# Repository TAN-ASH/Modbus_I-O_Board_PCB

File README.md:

# Modbus_I-O_Board_PCB
Modbus Protocol based Input/output board to control periphery

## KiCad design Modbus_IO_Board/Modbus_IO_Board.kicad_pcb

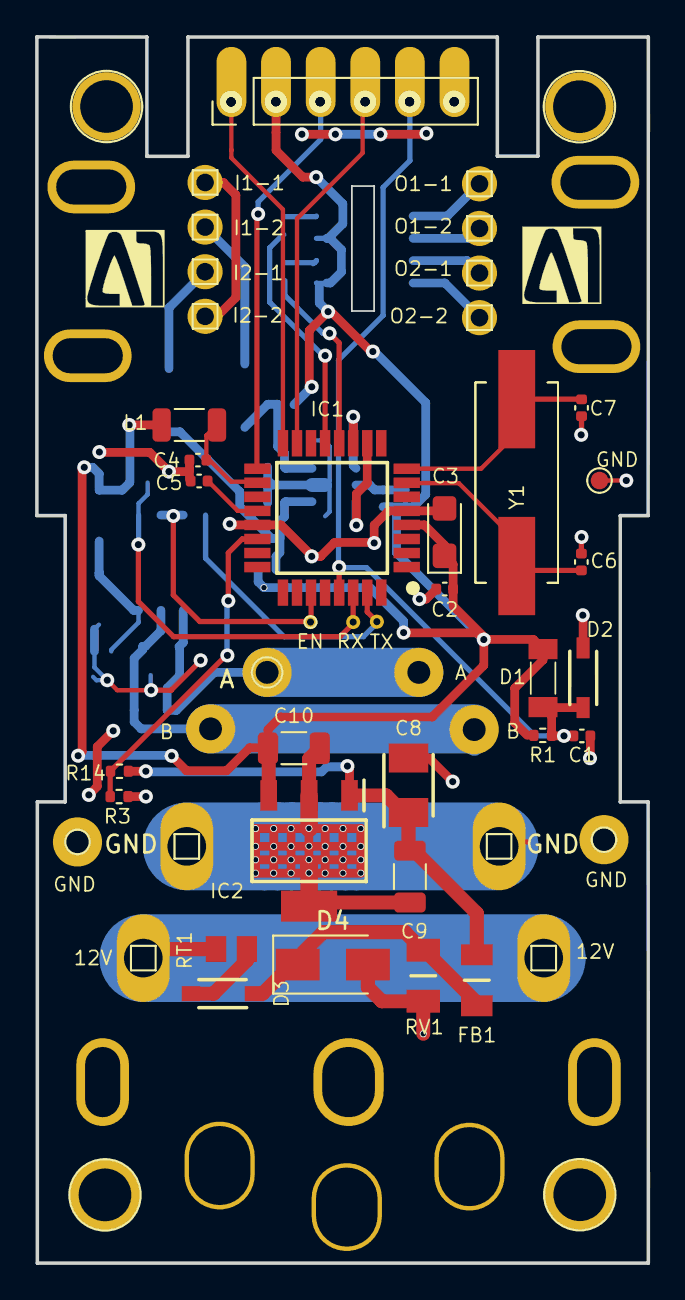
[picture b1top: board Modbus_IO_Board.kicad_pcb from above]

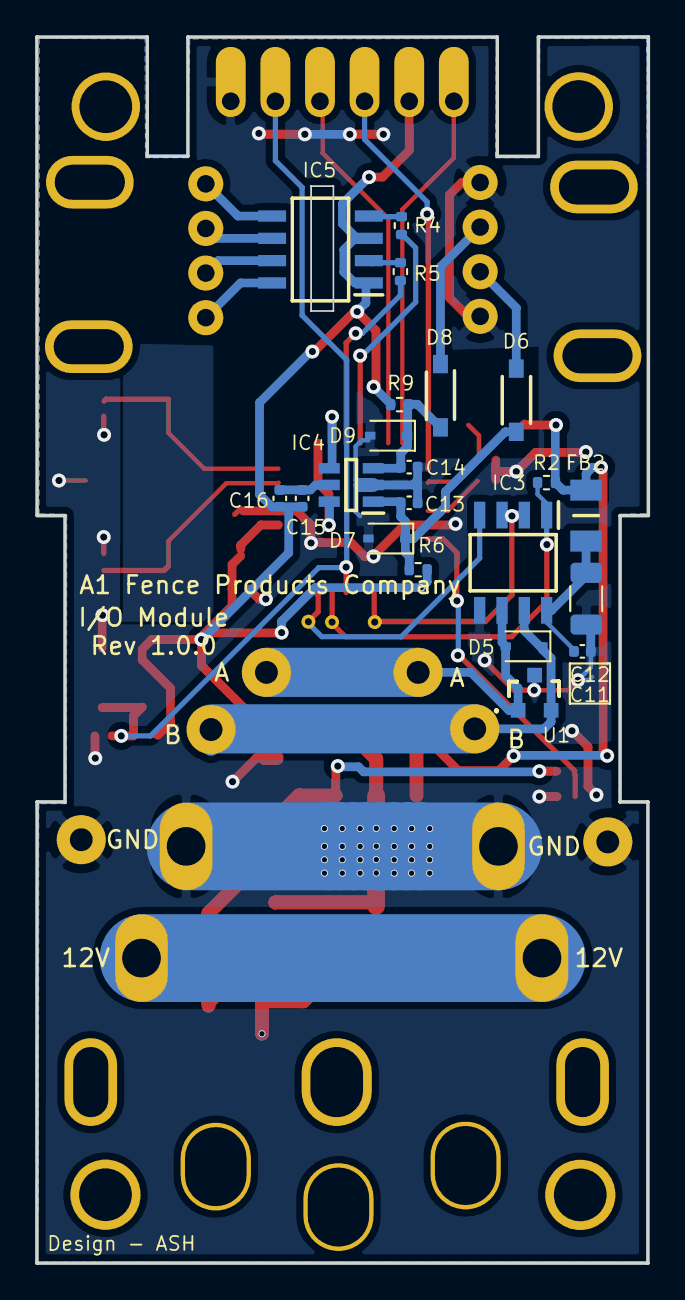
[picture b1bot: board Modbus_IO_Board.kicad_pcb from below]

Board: 2 copper layers, 34.8 x 69.8 mm, 76 parts (21 on the bottom side), 36 nets.

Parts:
12V, 12V#2: TestPoint; TestPoint_THTPad_1.0x1.0mm_Drill0.5mm
A: TestPoint; TestPoint_THTPad_1.0x1.0mm_Drill0.5mm
B: TestPoint; TestPoint_THTPad_1.0x1.0mm_Drill0.5mm
B#2: TestPoint; TestPoint_THTPad_1.0x1.0mm_Drill0.5mm
C1, C16: 1uF; C_0402_1005Metric
C2: 10nF; C_0402_1005Metric
C3: 1uF; CP_EIA-3216-18_Kemet-A
C4, C5, C11, C13, C14: 100nF; C_0402_1005Metric
C6, C7: 22pF; C_0402_1005Metric
C8: 10uF35V; CAPPM3528X210N
C9: 0.1uF35V; C_1206_3216Metric
C10: 4.7uF10V; C_1206_3216Metric
C12: 4.7uF; C_1206_3216Metric
C15: 0.1uF; C_0402_1005Metric
D1: D; FDLL4448
D2: D_Zener; SOD3716X145N
D3, D6, D8: B5819W-TP; SOD3716X135N
D4: D_TVS; D_SMA
D5, D7, D9: D_TVS; D_SOD-323
EN: TestPoint; TestPoint_Pad_D1.0mm
FB1, FB2: 74279218; BEADC3216X130N
GND: TestPoint; TestPoint_Pad_D1.0mm
GND#2, GND#3: TestPoint; TestPoint_Pad_D1.0mm
H1, H2, H3, H4: MountingHole; TestPoint_Plated_Hole_D3.0mm
I1-1, I1-2, I2-1, I2-2: TestPoint; TestPoint_THTPad_1.0x1.0mm_Drill0.5mm
IC1: ATMEGA328PB-AN; QFP80P900X900X120-32N
IC2: TPS7B6933QDCYRQ1; SOT230P700X180-4N
IC3: MAX3072EASA+; SOIC127P600X175-8N
IC4: SN74LVC2G14DBVRG4; SOT95P280X145-6N
IC5: LTV-206; SOIC127P610X363-8N
J1: Conn_01x06_Male; PinSocket_1x06_P2.54mm_Vertical
L1: 10uH; L_1206_3216Metric
O1-1, O1-2, O2-1, O2-2: TestPoint; TestPoint_THTPad_1.0x1.0mm_Drill0.5mm
R1, R2, R14: 4K7; R_0402_1005Metric
R3: 100K; R_0402_1005Metric
R4, R5: 330; R_0402_1005Metric
R6, R9: 4.7K; R_0402_1005Metric
RT1: PRG21BC4R7MM1RA; THRMC2012X110N
RV1: Varistor; VARC3216X145N
RX: TestPoint; TestPoint_Pad_D1.0mm
TP9, TP11, TP15: TestPoint; TestPoint_THTPad_1.0x1.0mm_Drill0.5mm
TP18: TestPoint; TestPoint_Pad_D1.0mm
U1: PSM712-LF-T7; PSM712LFT7
Y1: 7.37MHz; ABLS373728MHZD4YT
e: CONN_01X01; 1pin
e#2, e#3, e#4: CONN_01X01; 1pin

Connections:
+3V3: C2.1, C3.1, C10.1, C15.1, C16.1, D1.1, FB2.2, IC1.4, IC2.3, IC5.1, IC5.3, J1.2, L1.1, R1.1, R2.1, R6.1, R9.1
+12V: 12V.1, 12V#2.1, RT1.1
/1A: C13.1, D6.2, D7.1, IC4.1, R6.2
/1Y: IC1.10, IC4.6
/2A: C14.1, D8.2, D9.1, IC4.3, R9.2
/2Y: IC1.11, IC4.4
/Data_A: A.1, D5.2, IC3.6, TP9.1, U1.1
/Data_B: B.1, B#2.1, D5.1, IC3.7, U1.2
/MAX_EN: EN.1, IC1.27, IC3.2, IC3.3
/MISO: IC1.16, J1.1
/MOSI: IC1.15, J1.4
/OUT1: IC1.12, R5.1
/OUT2: IC1.13, R4.1
/RSB: C1.1, D1.2, D2.1, IC1.29, J1.5, R1.2
/RXD: IC1.30, IC3.1, R2.2, RX.1
/SCK: IC1.17, J1.3
/TXD: IC1.31, IC3.4, TP18.1
/Vin: IC1.22, R3.2, R14.1
GND: C1.2, C2.2, C3.2, C4.1, C5.2, C6.2, C7.2, C8.2, C9.2, C10.2, C11.2, C12.2, C13.2, C14.2, D2.2, D4.2, D7.2, D9.2, GND.1, GND#2.1, GND#3.1, I1-1.1, I2-2.1, IC1.5, IC1.21, IC2.2, IC2.4, IC3.5, IC4.2, J1.6, R14.2, RV1.2, TP11.1, TP15.1, U1.3
unnamed: C4.2, IC1.20
unnamed: C5.1, IC1.18, L1.2
unnamed: C6.1, IC1.7, Y1.1
unnamed: C7.1, IC1.8, Y1.2
unnamed: C8.1, C9.1, FB1.2, IC2.1, R3.1
unnamed: C11.1, C12.1, FB2.1, IC3.8
unnamed: C15.2, C16.2, IC4.5
unnamed: D3.1, D4.1, FB1.1, RV1.1
unnamed: D3.2, RT1.2
unnamed: D6.1, I2-1.1
unnamed: D8.1, I1-2.1
unnamed: IC5.2, R5.2
unnamed: IC5.4, R4.2
unnamed: IC5.5, O1-1.1
unnamed: IC5.6, O1-2.1
unnamed: IC5.7, O2-1.1
unnamed: IC5.8, O2-2.1

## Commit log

2021-10-25 IO module Rev 1.0.0
